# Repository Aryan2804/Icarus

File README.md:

# Icarus
Design an FPV quadcopter from scratch using brushed coreless motors
|   |
:-------------------------:|

## Table of Contents:
- [About The Project](#about-the-project)
- [Components](#components)
- [Perfboard Testing](#perfboard-testing)
- [PCB Model](#pcb-model)
- [Software Used](#software-used)
- [Resources](#resources)
- [Contributors](#contributors)

## About the Project:
The aim of this project is to design and assemble a full size fpv drone operating over bluetooth which will use firmware that is written from scratch

## Repository structure:

```
Icarus
├── Docs
│   ├── components.md
│   └── resources.md
├── Firmware                      # ESP-IDF firmware, written from scratch
│   ├── IMU                       # BMI088 driver + sensor fusion
│   ├── Motor_Control             # PWM/ESC logic for 8520 brushed motors
│   ├── Camera                    # Xiao-ESP32-S3-Sense (OV3660) interface
│   └── Main                      # control loop
├── Hardware
│   ├── PCB                       # KiCad 10.0 files
│   │   ├── Schematics
│   │   ├── Gerbers
│   │   └── 3D_Views
│   └── Mechanical                # Onshape exports (frame, mounts)
│       └── STL
├── Testing
│   ├── Perfboard                 # Perfboard prototype 
│   └── Loadcell                  # Motor thrust test 
├── assets                        # Images used in README
└── README.md
```

## Components:

|     Components        |          Description          |
| --------------------- | ----------------------------- |
|ESP32-S3-Wroom-1 board |Microcontroller|
|8520 Brushed motors |Motors for Propulsion|
|BMI 088 |6-DoF Inertial Measurement Unit|
|Xiao-ESP32-S3-sense OV3660 |Camera Module|
|USB- C Receptacle |Power and Programming Interface|
|AMS1117 |Voltage regulator|
|Load cell |Thrust measurement|

## Perfboard and Load cell Testing:
|   |  | 
:-------------------------:|:-------------------------:|

## PCB Model:
- View of the PCB Model front and back:       
  
|             |  |    
:-------------------------:|:-------------------------:|

- View of the PCB Routing - front and back:      
  
|             |  |  
:-------------------------:|:-------------------------:|

## Software Used: 
- Mechanical Design - [Onshape](https://www.onshape.com/en/)
- PCB Design - [KiCad 10.0](https://www.kicad.org/)
- Embedded C and Firmware - [ESP-IDF](https://docs.espressif.com/projects/esp-idf/en/stable/esp32/get-started/index.html)
- Simulation - [Ardupilot](https://ardupilot.org/planner/docs/mission-planner-installation.html)

## Resources:
- [Sergio Virahonda's blog](https://medium.com/@svirahonda/building-a-drone-flight-controller-from-scratch-a-software-engineers-guide-to-clean-c-644a2bd392c4) 
- [Understanding SPI protocol](https://www.youtube.com/watch?v=0nVNwozXsIc&t=119s)
- [Undestanding the IMU](https://www.kynix.com/components/the-ultimate-guide-to-the-bosch-bmi088-sensor-7-key-insights.html)
- [Understanding KiCad](https://www.youtube.com/watch?v=XiLnHYSrNHw) 

## Contributors:
- [Roshan Castelino](https://github.com/roshan-castelino)
- [Aryan Ghughare](https://github.com/Aryan2804)
- [Astha Sharma ](https://github.com/asthasharma020406-stack)

## License:
[MIT License](https://opensource.org/license/mit/)

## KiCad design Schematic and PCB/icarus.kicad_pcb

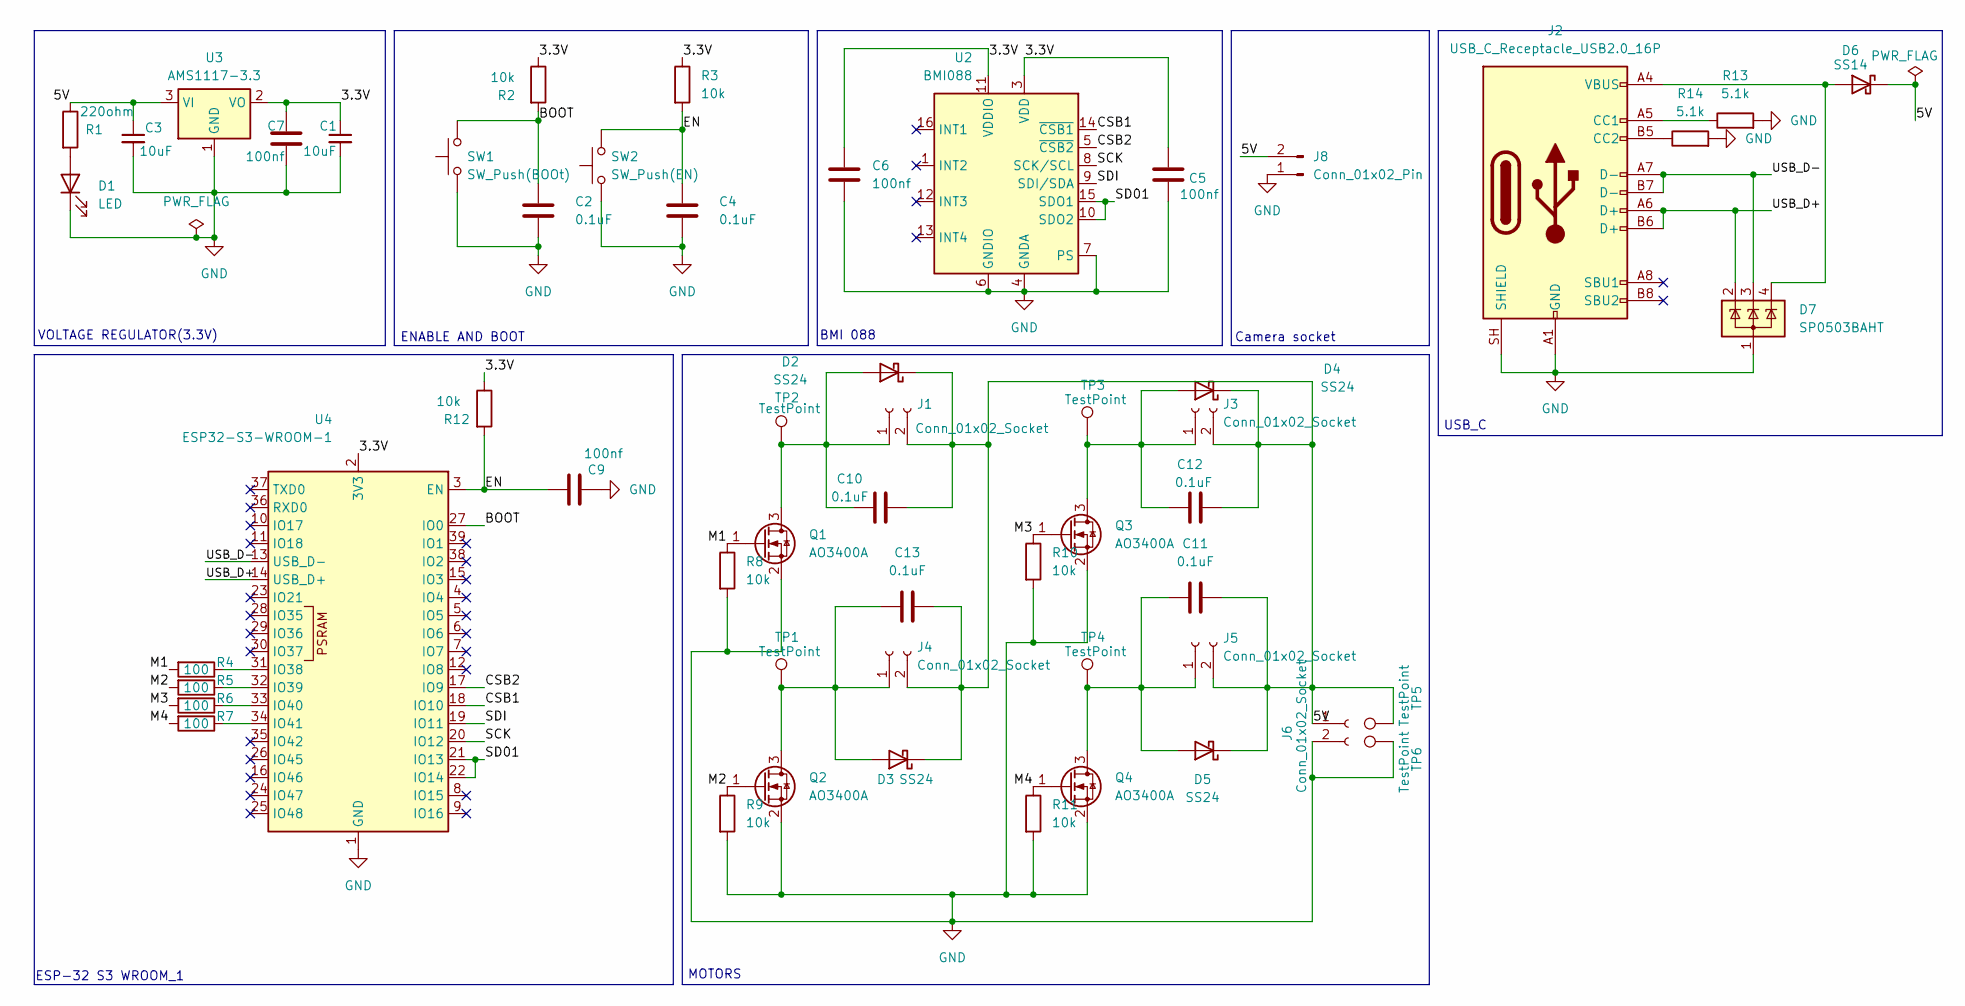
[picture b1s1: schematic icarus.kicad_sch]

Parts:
C1, C3: 10uF; C_0805_2012Metric
C2, C4: 0.1uF; C_0603_1608Metric
C5, C6, C9: 100nf; C_0603_1608Metric
C7: 100nf; C_0805_2012Metric
C10, C11, C12, C13: 0.1uF; C_1206_3216Metric
D1: LED; LED_0603_1608Metric_Pad1.05x0.95mm_HandSolder
D2, D3, D4, D5: SS24; D_SMA
D6: SS14; D_SMA
D7: SP0503BAHT; SOT-143
J1, J3, J4, J5, J6: Conn_01x02_Socket; JST_EH_B2B-EH-A_1x02_P2.50mm_Vertical
J2: USB_C_Receptacle_USB2.0_16P; USB_C_Receptacle_GCT_USB4105-xx-A_16P_TopMnt_Horizontal
J8: Conn_01x02_Pin; JST_SH_SM02B-SRSS-TB_1x02-1MP_P1.00mm_Horizontal
Q1, Q2, Q3, Q4: AO3400A; SOT-23
R1: 220ohm; R_0603_1608Metric
R2, R3, R8, R9, R10, R11, R12: 10k; R_0603_1608Metric
R4, R5, R6, R7: 100; R_0603_1608Metric
R13, R14: 5.1k; R_0603_1608Metric
SW1: SW_Push(BOOt); SW_Push_SPST_NO_Alps_SKRK
SW2: SW_Push(EN); SW_Push_SPST_NO_Alps_SKRK
TP1, TP2, TP3, TP4: TestPoint; TestPoint_Pad_1.0x1.0mm
TP5, TP6: TestPoint; TestPoint_THTPad_2.0x2.0mm_Drill1.0mm
U2: BMI088; Bosch_LGA-16_4.5x3mm_P0.5mm_LayoutBorder7x1y_ClockwisePinNu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
U3: AMS1117-3.3; SOT-223-3_TabPin2
U4: ESP32-S3-WROOM-1

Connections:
/3.3V: C1.1, C5.1, C6.1, C7.1, R2.1, R3.1, R12.1, U2.3 (VDD), U2.11 (VDDIO), U3.2 (VO), U4.2 (3V3)
/5V: C3.1, C10.1, C11.1, C12.1, C13.1, D2.1 (K), D3.1 (K), D4.1 (K), D5.1 (K), D6.1 (K), J1.2, J3.2, J4.2, J5.2, J6.1, J8.2, R1.1, TP5.1 (1_1), U3.3 (VI)
/BOOT: C2.1, R2.2, SW1.2, U4.27 (IO0); also elsewhere on the board
/CSB1: U2.14 (~CSB1), U4.18 (IO10)
/CSB2: U2.5 (~CSB2), U4.17 (IO9)
/EN: C4.1, C9.2, R3.2, R12.2, SW2.2, U4.3 (EN); also elsewhere on the board
/M1: Q1.1 (G), R4.2, R8.1
/M2: Q2.1 (G), R5.2, R9.1
/M3: Q3.1 (G), R6.2, R10.1
/M4: Q4.1 (G), R7.2, R11.1
/SCK: U2.8 (SCK/SCL), U4.20 (IO12)
/SD01: U2.10 (SDO2), U2.15 (SDO1), U4.21 (IO13), U4.22 (IO14)
/SDI: U2.9 (SDI/SDA), U4.19 (IO11)
/USB_D+: D7.2 (K), J2.A6 (D+), J2.B6 (D+), U4.14 (USB_D+)
/USB_D-: D7.3 (K), J2.A7 (D-), J2.B7 (D-), U4.13 (USB_D-)
GND: C1.2, C2.2, C3.2, C4.2, C5.2, C6.2, C7.2, C9.1, D1.1 (K), D7.1 (A), J2.A1 (GND), J2.A12 (GND), J2.B1 (GND), J2.B12 (GND), J2.SH (SHIELD), J6.2, J8.1, Q1.2 (S), Q2.2 (S), Q3.2 (S), Q4.2 (S), R8.2, R9.2, R10.2, R11.2, R13.2, R14.2, SW1.1, SW2.1, TP6.1 (1_1), U2.2 (GNDA), U2.4 (GNDA), U2.6 (GNDIO), U2.7 (PS), U3.1 (GND), U4.1 (GND), U4.40 (GND), U4.41 (GND); also elsewhere on the board
unnamed: D1.2 (A), R1.2
unnamed: C10.2, D2.2 (A), J1.1, Q1.3 (D), TP2.1 (1_1)
unnamed: C13.2, D3.2 (A), J4.1, Q2.3 (D), TP1.1 (1_1)
unnamed: C12.2, D4.2 (A), J3.1, Q3.3 (D), TP3.1 (1_1)
unnamed: C11.2, D5.2 (A), J5.1, Q4.3 (D), TP4.1 (1_1)
unnamed: D6.2 (A), D7.4 (K), J2.A4 (VBUS), J2.A9 (VBUS), J2.B4 (VBUS), J2.B9 (VBUS)
unnamed: J2.A5 (CC1), R13.1
unnamed: J2.B5 (CC2), R14.1
unnamed: R4.1, U4.31 (IO38)
unnamed: R5.1, U4.32 (IO39)
unnamed: R6.1, U4.33 (IO40)
unnamed: R7.1, U4.34 (IO41)

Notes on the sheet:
VOLTAGE REGULATOR(3.3V)
ENABLE AND BOOT
USB_C
ESP-32 S3 WROOM_1
MOTORS
BMI 088
Camera socket

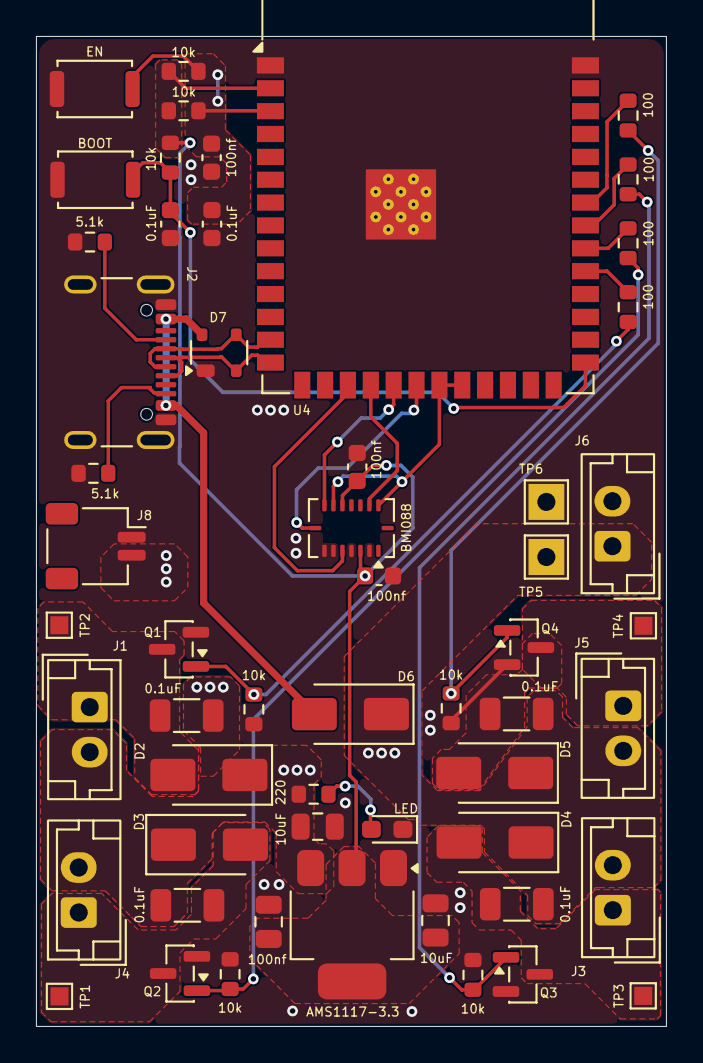
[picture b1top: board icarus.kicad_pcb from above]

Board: 2 copper layers, 35.0 x 55.0 mm, 55 parts (0 on the bottom side), 28 nets.

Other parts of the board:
BOOT: SW_Push(BOOt); SW_Push_SPST_NO_Alps_SKRK
EN: SW_Push(EN); SW_Push_SPST_NO_Alps_SKRK

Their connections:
/BOOT: BOOT.2; also elsewhere on the board
/EN: EN.2; also elsewhere on the board
GND: BOOT.1, EN.1; also elsewhere on the board
